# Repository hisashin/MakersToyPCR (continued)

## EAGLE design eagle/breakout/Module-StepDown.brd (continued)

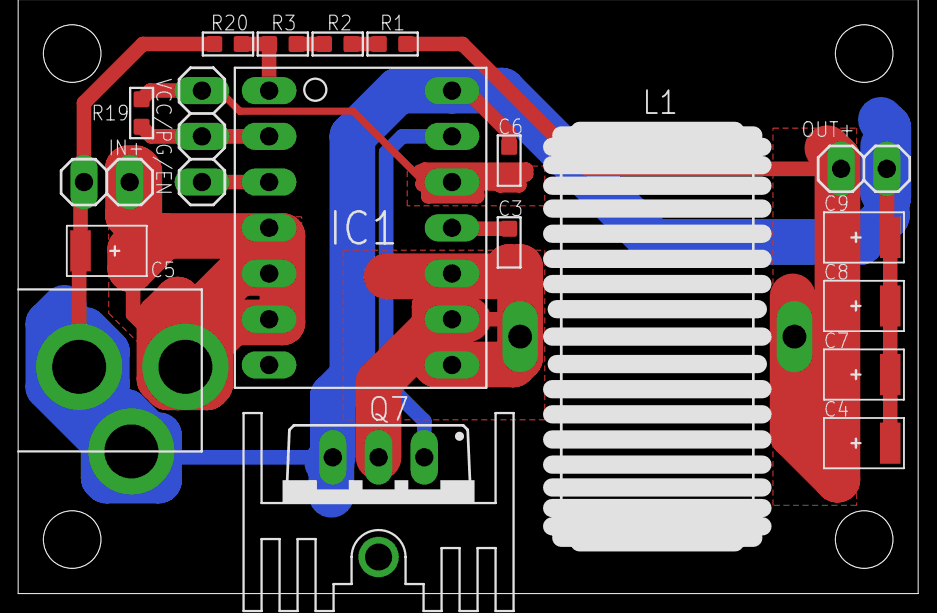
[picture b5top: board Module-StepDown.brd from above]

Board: 2 copper layers, 20 parts (0 on the bottom side), 12 nets.

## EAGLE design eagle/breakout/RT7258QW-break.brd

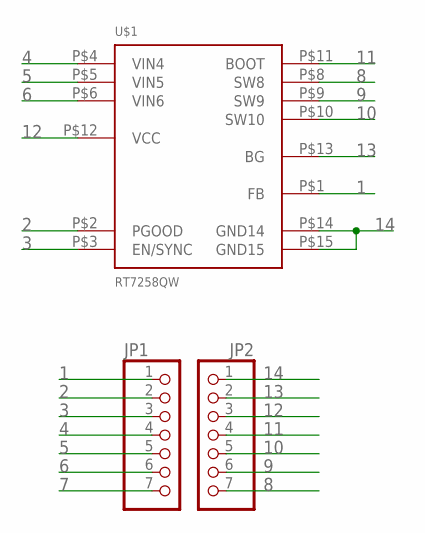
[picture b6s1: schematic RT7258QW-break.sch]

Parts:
JP1, JP2: PINHD-1X7; 1X07
U$1: RT7258QW; RT7258GQW

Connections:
1: JP1.1, U$1.P$1 (FB)
2: JP1.2, U$1.P$2 (PGOOD)
3: JP1.3, U$1.P$3 (EN/SYNC)
4: JP1.4, U$1.P$4 (VIN4)
5: JP1.5, U$1.P$5 (VIN5)
6: JP1.6, U$1.P$6 (VIN6)
7: JP1.7
8: JP2.7, U$1.P$8 (SW8)
9: JP2.6, U$1.P$9 (SW9)
10: JP2.5, U$1.P$10 (SW10)
11: JP2.4, U$1.P$11 (BOOT)
12: JP2.3, U$1.P$12 (VCC)
13: JP2.2, U$1.P$13 (BG)
14: JP2.1, U$1.P$14 (GND14), U$1.P$15 (GND15)

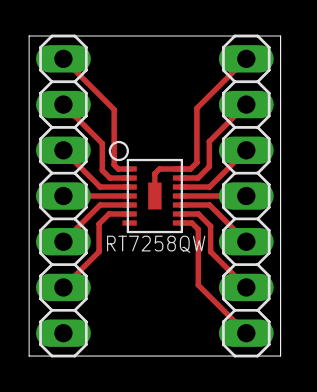
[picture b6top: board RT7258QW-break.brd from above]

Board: 2 copper layers, 3 parts (0 on the bottom side), 13 nets.

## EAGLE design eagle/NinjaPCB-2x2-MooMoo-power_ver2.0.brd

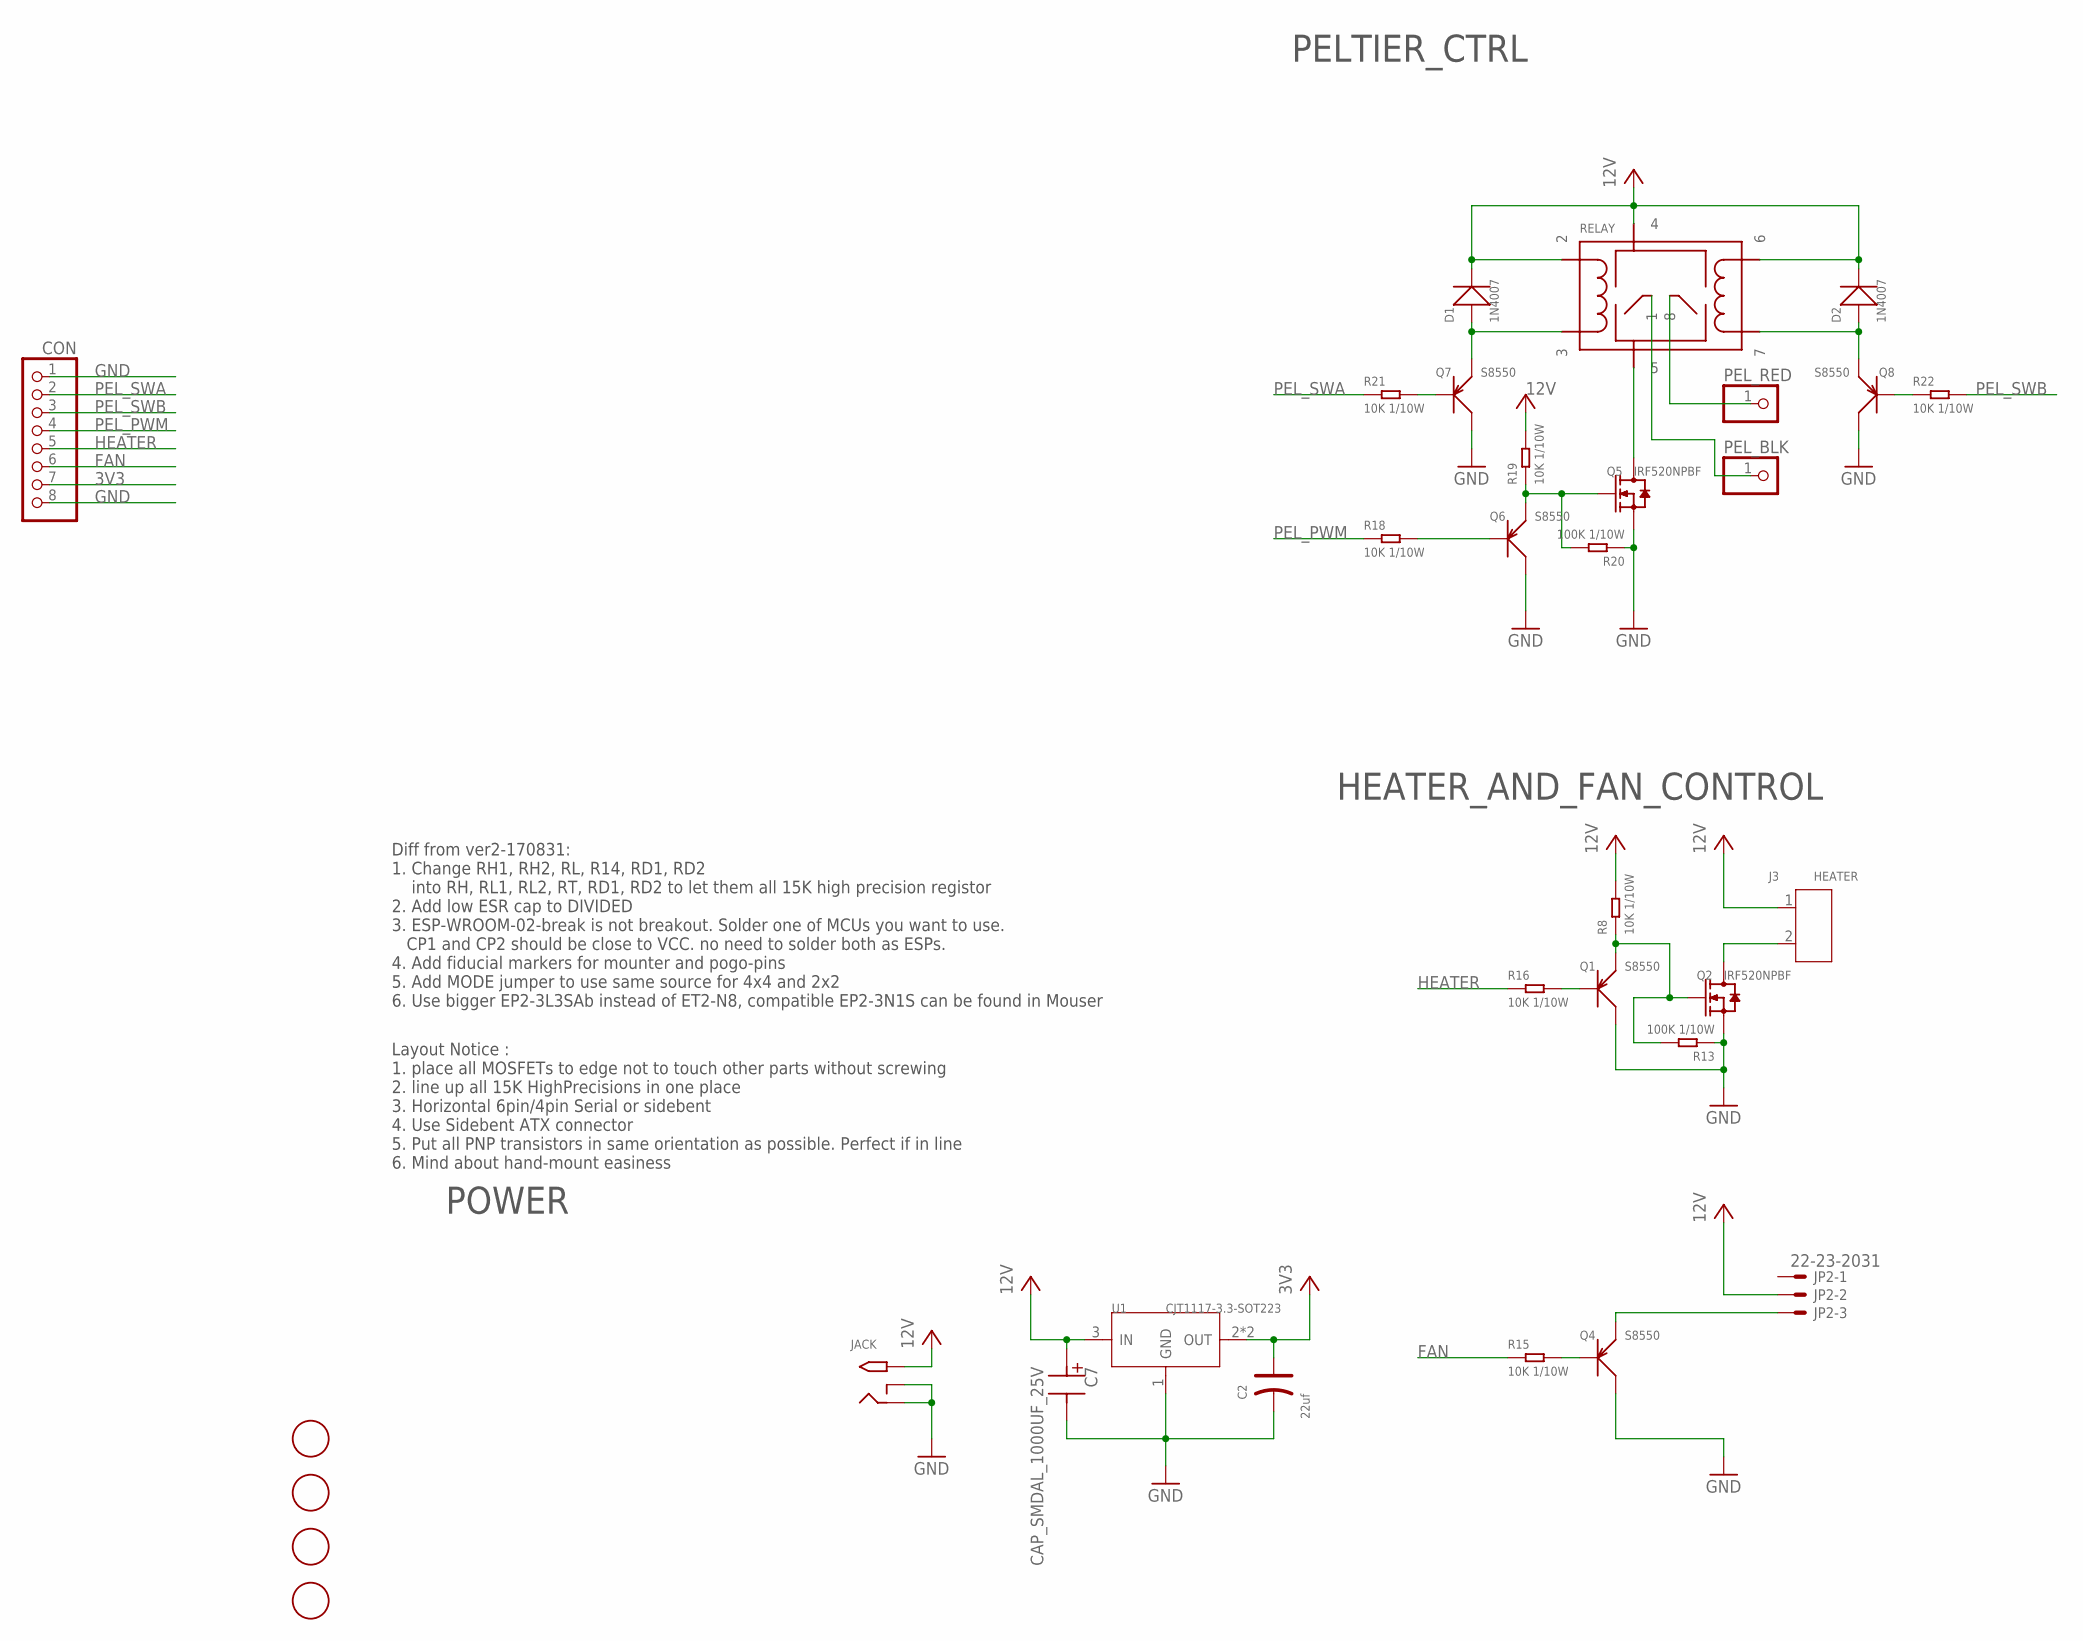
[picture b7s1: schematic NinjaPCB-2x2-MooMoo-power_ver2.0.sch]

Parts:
C2: 22uf; AVX-B
C7: CAP_SMDAL_1000UF_25V; CAP_SMD_AL_D125
CON: PINHD-1X8; 1X08
D1, D2: 1N4007; DO-214AC
J3: HEATER; H2-3.5-7.0X7.0MM
JACK: 2.1MMJACKTHM; PJ-102A
JP2: 22-23-2031
PEL_BLK: PINHD-1X1L; 1X01LONG
PEL_RED: PINHD-1X1L; 1X01LONG
Q1, Q4, Q6, Q7, Q8: S8550; SOT-23
Q2, Q5: IRF520NPBF; TO-220
R8, R15, R16, R18, R19, R21, R22: 10K 1/10W; R0603
R13, R20: 100K 1/10W; R0603
RELAY: NEC-RELAY2EP2; NEC-EP2
U1: CJT1117-3.3-SOT223; SOT-223
U$3, U$4, U$5, U$6: FIDUCIAL; FIDUCIAL_1MM

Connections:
3V3: C2.+, U1.2 (OUT), U1.TER (OUT)
12V: C7.P$P, D1.2 (-), D2.2 (-), J3.1, JACK.TIP, JP2.2, R8.2, R19.2, RELAY.P$2 (2), RELAY.P$4 (4), RELAY.P$6 (6), U1.3 (IN)
FAN: R15.1
GND: C2.-, C7.P$M, CON.1, JACK.RING, JACK.RING_SW, Q1.3 (C), Q2.3 (S), Q4.3 (C), Q5.3 (S), Q6.3 (C), Q7.3 (C), Q8.3 (C), R13.1, R20.1, U1.1 (GND)
HEATER: R16.1
unnamed: JP2.3, Q4.2 (E)
unnamed: J3.2, Q2.2 (D), Q2.HEAT (D)
unnamed: Q5.2 (D), Q5.HEAT (D), RELAY.P$5 (5)
unnamed: Q5.1 (G), Q6.2 (E), R19.1, R20.2
unnamed: PEL_RED.1, RELAY.P$8 (8)
unnamed: PEL_BLK.1, RELAY.P$1 (1)
unnamed: Q1.2 (E), Q2.1 (G), R8.1, R13.2
unnamed: Q6.1 (B), R18.2
unnamed: Q4.1 (B), R15.2
unnamed: Q1.1 (B), R16.2
unnamed: D1.1 (+), Q7.2 (E), RELAY.P$3 (3)
unnamed: Q7.1 (B), R21.2
unnamed: Q8.1 (B), R22.1
unnamed: D2.1 (+), Q8.2 (E), RELAY.P$7 (7)
PEL_PWM: R18.1
PEL_SWA: R21.1
PEL_SWB: R22.2

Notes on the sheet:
HEATER_AND_FAN_CONTROL
PELTIER_CTRL
POWER
Diff from ver2-170831: 1. Change RH1, RH2, RL, R14, RD1, RD2 into RH, RL1, RL2, RT, RD1, RD2 to let them all 15K high precision registor 2. Add low ESR cap to DIVIDED 3. ESP-WROOM-02-break is not breakout. Solder one of MCUs you want to use. CP1 and CP2 should be close to VCC. no need to solder bot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
Layout Notice : 1. place all MOSFETs to edge not to touch other parts without screwing 2. line up all 15K HighPrecisions in one place 3. Horizontal 6pin/4pin Serial or sidebent 4. Use Sidebent ATX connector 5. Put all PNP transistors in same orientation as possible. Perfect if in line 6. Mind about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

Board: 2 copper layers, 32 parts (0 on the bottom side), 17 nets, no tracks yet.

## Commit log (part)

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2014-08-18 Detailing REAME
2014-12-01 Fix but in port scanning code
2014-12-01 Add syncFileSystem permission to manifest file (chrome)
2014-12-01 Modify .gitignore by adding *~ (emacs tmp files)
2014-12-01 Add test buttons & skeleton of dev code
2014-12-02 Check quota of sync filesystem
2015-03-05 Correct the firmware version
    * Correct the firmware version in resource files to stop showing wrong "update" dialog
    * Add version
    * Fix a typo in the build shell
2015-03-05 Add nde debug feature
    * Replace console.log, info, warn, error with custom functions
    * Add debug textarea to the top panel
2015-03-05 Add version (1.1.4 -> 1.1.5)
2015-03-05 Fix build shell script
2015-08-04 add pcbs
2015-08-04 add readme
2015-08-04 refresh all data to latest
2015-08-05 write BOM url clearly
2015-10-19 remove unused pcbs
2015-10-20 rename for easy understanding
2015-10-22 link to wiki
2015-12-18 export lasercut data as ai and pdf
2016-01-06 add values of reg&cap
2016-02-05 update sheet->grease
2016-02-07 add tapping instructions
2016-03-06 add handle
2016-11-12 Use same values in sch and brd
2016-11-12 remove unused files
2016-11-20 well block is updated to hold tubes perfectly
2016-11-20 CAM of well added
2016-11-26 update toolpath Tube2
2017-06-19 Show alert section when opened as a web page
2017-06-28 Fix compilation error with ESP8266
2017-07-01 Add WiFi demo code
    * Fix compilation problem
    * Add WiFi edition specific config
2017-07-03 Use abstract class "Communicator"
2017-07-04 Implement JSONP communication system
2017-07-04 Test WiFi + JSONP
2017-07-05 Implement WiFi + Browser app communication
2017-07-05 Implement storage functionalities for WiFi edition
2017-07-05 Use TOUT pin of ESP8288
2017-07-05 Use on/off control to control lid heater
2017-07-06 Implement firmware verison checker
2017-09-02 preparing NinjaPCB ver2 using Seeed OPL
2017-09-02 fixing things
2017-09-28 add evaluation board for NinjaPCB ver2
2017-10-04 Define analog switch pin for 2-range temperature measurement
2017-10-04 Switch WiFi mode with HIGH_TEMP pin
2017-10-04 Implement AP mode logic
2017-10-04 Save & load wifi connection information
2017-10-04 Add link to PCR configuration guide
2017-10-05 Refactor / Implement IP address notification system
2017-10-05 Compare IP address
2017-10-06 completed ver2-170831
2017-10-09 ordered pcb
2017-10-12 Implement WiFi init functionalities
2017-12-01 remove ver2 temporary. it will be back after evaluation.
2017-12-12 Support two types of ADC (SPI MCP3554 & NAU7803)
2017-12-27 Fix AP mode bug
2018-01-02 Implement OTA sequence
2018-01-11 pushed again to share with mariko. do not manufacture it yet
2018-01-16 add memos
2018-01-17 pulldown HEATER to write
2018-01-17 VNH5019 doesnot have same pinout as VNH3SP30
2018-01-23 Implement I2C ADC
2018-01-29 use relay instead of driver
2018-01-29 remove images of first version
2018-01-29 add ESP-12F-breakout compatible with ESP-WROOM-02-breakout
2018-01-29 use breakout board
2018-02-08 latest updates
2018-02-27 Designing 2nd ver2 board. DO NOT make first NinjaPCB_ver2-170831.brd
2018-03-03 finished
2018-03-03 remove errored one
2018-03-03 to be ordered
2018-03-04 npn to pnp. added pullups and pulldowns
2018-03-04 added hole for gromet #digikey 36-733-ND
2018-03-08 version control
2018-03-08 changed R14 into RT. no reason for T
2018-03-08 add low ESR cap to standard voltage for NAU7802
2018-03-09 Support Relay (for replacement of motor driver IC)
2018-03-13 replace 2d data to ver2 dxf
2018-03-15 add MODE jumper to use same source for 4x4 and 2x2
2018-03-15 add MooMoo ones
2018-03-16 split into 2 subprojects : 4x4 NinNin and 2x2 MooMoo
2018-03-17 use easier parts. add notes to design
2018-03-18 abstract layout image of 2x2MooMoo
2018-03-19 Implement mDNS functionalities
2018-03-22 change values of MOSFET G-S reg
2018-03-26 start wiring NinNin ver2.0
2018-03-30 wired
2018-03-30 dru clear
2018-03-30 minor tunes
2018-03-31 ready to order
2018-04-01 panelized NinNin
2018-04-01 prepare for order
2018-04-04 ordered
2018-04-05 Fix NAU7802 library
2018-04-05 Rename NAU7803->NAU7802
2018-04-08 shrink panel
2018-04-11 Implement local test
2018-04-11 set distance more equal 10mil for 2oz at Seeed
2018-04-12 Fix bugs (PID related logic, relay control etc.)
2018-04-17 Amplification test
2018-04-18 set default 4x4
2018-04-19 remove wrong schematics
2018-04-19 reset
2018-04-26 Implement WiFi communication / bug fix
2018-04-26 Update lasercut data
2018-04-26 add svg
2018-04-26 update 2d/3d info
2018-04-26 add eps
2018-04-27 Enhance network functionalities
2018-05-01 Simplify WiFi related code
2018-05-01 CDN test
2018-05-01 add image
2018-05-02 Organize constants related to thermistors and their counter resistors
2018-05-03 Amplification demo
2018-05-06 Implement sample temp estimation logic
2018-05-10 Separate OTA logic as Update.ino# Please enter the commit message for your changes. Lines starting
2018-05-10 Remove unused file
2018-05-10 Add binary
2018-05-10 Enhance OTA functionalities
2018-05-14 Fixed board config according to 2.0 schematics
2018-05-14 Restart device after saving WiFi config
2018-05-14 update dxf
2018-05-17 Implemented SSL update
2018-05-17 Add Update logic files
2018-05-17 Prepare for thermistor ADC improvement
2018-05-17 Implement basic switching logic
2018-05-17 Implement well<=>lid ADC switching logic
2018-05-21 ver2.1 finished
2018-05-23 minor update of silk
2018-05-25 minor update for layout
2018-05-29 Imprement ADC error handling
2018-05-30 Implemented hardware check for safety
2018-06-03 add manufacture
2018-06-03 update cdr
2018-06-03 share t5.0 model
2018-06-03 ignore autogen backup files of CorelDRAW
2018-06-12 Added error handling and WiFi reconnection feature
2018-06-12 Send error code
2018-06-14 .gitignore
2018-06-18 update laser
2018-06-19 cdr updated
2018-06-25 Implement hardware error detection
2018-06-27 PID tuning
2018-06-27 Implemented top page of server mode
2018-06-29 Support board 2.1
2018-06-29 Toggle debug message
2018-06-30 NinjaPCB ver2.2
2018-07-03 Stabilize ADC (especially in first boot)
2018-07-03 Display previous status/error of WiFi config
2018-07-03 Switch peltier pin in hardware init sequence
2018-07-06 Release 1.0.1
2018-07-06 Add rampElapsedTimeMsec to CyclerStatus struct
2018-07-06 Use ramping time when checking peltier device's health
2018-07-08 Use max and min temperature in hardware check
2018-07-08 Fix bug in peltier checker logic
2018-07-19 update front panel
2018-07-23 sync
2018-07-23 add NinjaPCR 2.2
2018-07-23 fixed NinjaPCB ver 2.2
2018-07-24 updated 2.2
2018-07-24 fixed 2.2
2018-07-24 remove zip from eagle
2018-08-09 add zip
2018-08-20 add models
2018-08-21 ChromeApp is out of support
2018-08-27 update words
2018-08-27 Add version
2018-08-27 remove chrome
2018-08-27 remove ver1.0
2018-10-17 Release firmware 1.0.12
    * Use ESP8266 2.4.2
    * Insert delay before resetting
2018-11-08 Pause heating units while processing HTTP requests
    * Change order of network and thermal cycler functions
    * Add "PauseHeatingUnits" function
    * Rename some members of Thermocycler class
2018-11-08 Remove unused functions
2018-11-08 Calculate and set power output ratio
2018-11-08 Use power outupt ratio when setting lid & peltier PWM values
    For safety, heating units are stopped while the HTTP server is responding.
    To compensate the off time, PWM values are amplified according to network
    response time.
2018-11-09 Fix bug (SetPowerOutputRatio was called in error handling block by mistake)
2018-11-09 Fix peltier driver bug
2018-11-10 Send signed value of Peltier drive instead of absolute value #11
2018-11-11 Consider balance of Peltier's internal heat and cooling efficiency
2018-11-11 Add version (1.0.13)
2018-11-13 Show MAC address on WiFi config view
2018-12-07 Add stubs of Pause/Resume/NextStep/NextCycle
2018-12-07 Implement pause/resume functionalities
    * Altered logic of calculating ramp & hold elapsed time
    * Parse commands from UI
    * Send response
2018-12-11 Send total cycles count and current cycle index
2019-01-10 Control next step/cycle flags
2019-01-10 Advance to next step by command
2019-01-10 Check if the step is "final" or not when receiving "next step" command
2019-01-24 Implement step/cycle skip
    * Accept next step / next cycle commands
    * Add version (1.1)
2019-01-27 Reconsider the hard-coded firmware server
    It would be more convenient if "firmwareHost" is set to the one that the machine is actually connected to, not the explicit host.
2019-03-19 AP mode
2019-03-20 Completed AP mode support
2019-04-03 add link to BOM
2019-04-15 Fix wrong error code / Add comments
2020-03-17 correct link
2020-04-13 remove unused data
2020-10-29 Add version / Fix "Error9" on very low temperature
2021-01-04 Fix threshold of hardware error detection logic
2021-03-31 Updated alert threshold of heating/cooling rate
2021-04-16 found another relay to H bridge but not wired
2021-04-16 add link
2021-05-10 add front panel to print for maker model
